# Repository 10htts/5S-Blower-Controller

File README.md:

# 5S Blower Controller

Open-source reference controller for a two-wire brushed-DC blower powered by a removable 5-series lithium-ion battery (approximately 15–21 V). The design uses a protected low-side N-MOSFET PWM stage, soft start, trigger filtering, voltage/current/temperature protection, an external physical fuse, and a latched fault requiring trigger release.

**Status: CAD CHECKS PASS; NOT YET APPROVED TO ORDER.** KiCad 10 reports zero DRC violations, zero unconnected items, zero schematic-parity issues, and zero ERC errors or warnings. The PCBWay review ZIP is generated, but motor, fuse, mechanical, transient, thermal, and first-article validation remain open. No regulatory certification is claimed.

See [architecture](docs/architecture.md), [wiring](docs/wiring.md), [safety](docs/safety.md), and [revision status](docs/revision-status.md). Firmware tests are host-side and do not replace hardware bring-up.

## Open and edit in KiCad

Open `hardware/blower-controller.kicad_pro` using **File → Open Existing Project** in KiCad. The project contains the editable schematic and PCB.

The canonical KiCad files are generated by `scripts/build_board.py`. A later regeneration will overwrite direct edits to the generated schematic and PCB, so save experimental manual edits under a different project name or port accepted changes into the generator and routing-repair sources.

## Rebuild and export

Run the deterministic board build with KiCad's bundled Python, then generate the current PCBWay review package:

```powershell
& "C:\Program Files\KiCad\10.0\bin\python.exe" scripts\build_board.py
python scripts\export_manufacturing.py --kicad-cli "C:\Program Files\KiCad\10.0\bin\kicad-cli.exe"
```

The current package is `manufacturing/pcbway-review-revC.zip`. It is suitable for PCBWay's Gerber viewer or quotation review, not authorization to place an order.

## Licensing

Hardware is licensed under CERN-OHL-S-2.0 (`LICENSE`). Firmware is GPLv3-or-later (`firmware/LICENSE`).

## Planned validation

Measure stall/start/run current, battery connector polarity, motor inductance, housing fit, fuse interruption behavior, and thermal rise before selecting production thresholds or ordering PCBs.

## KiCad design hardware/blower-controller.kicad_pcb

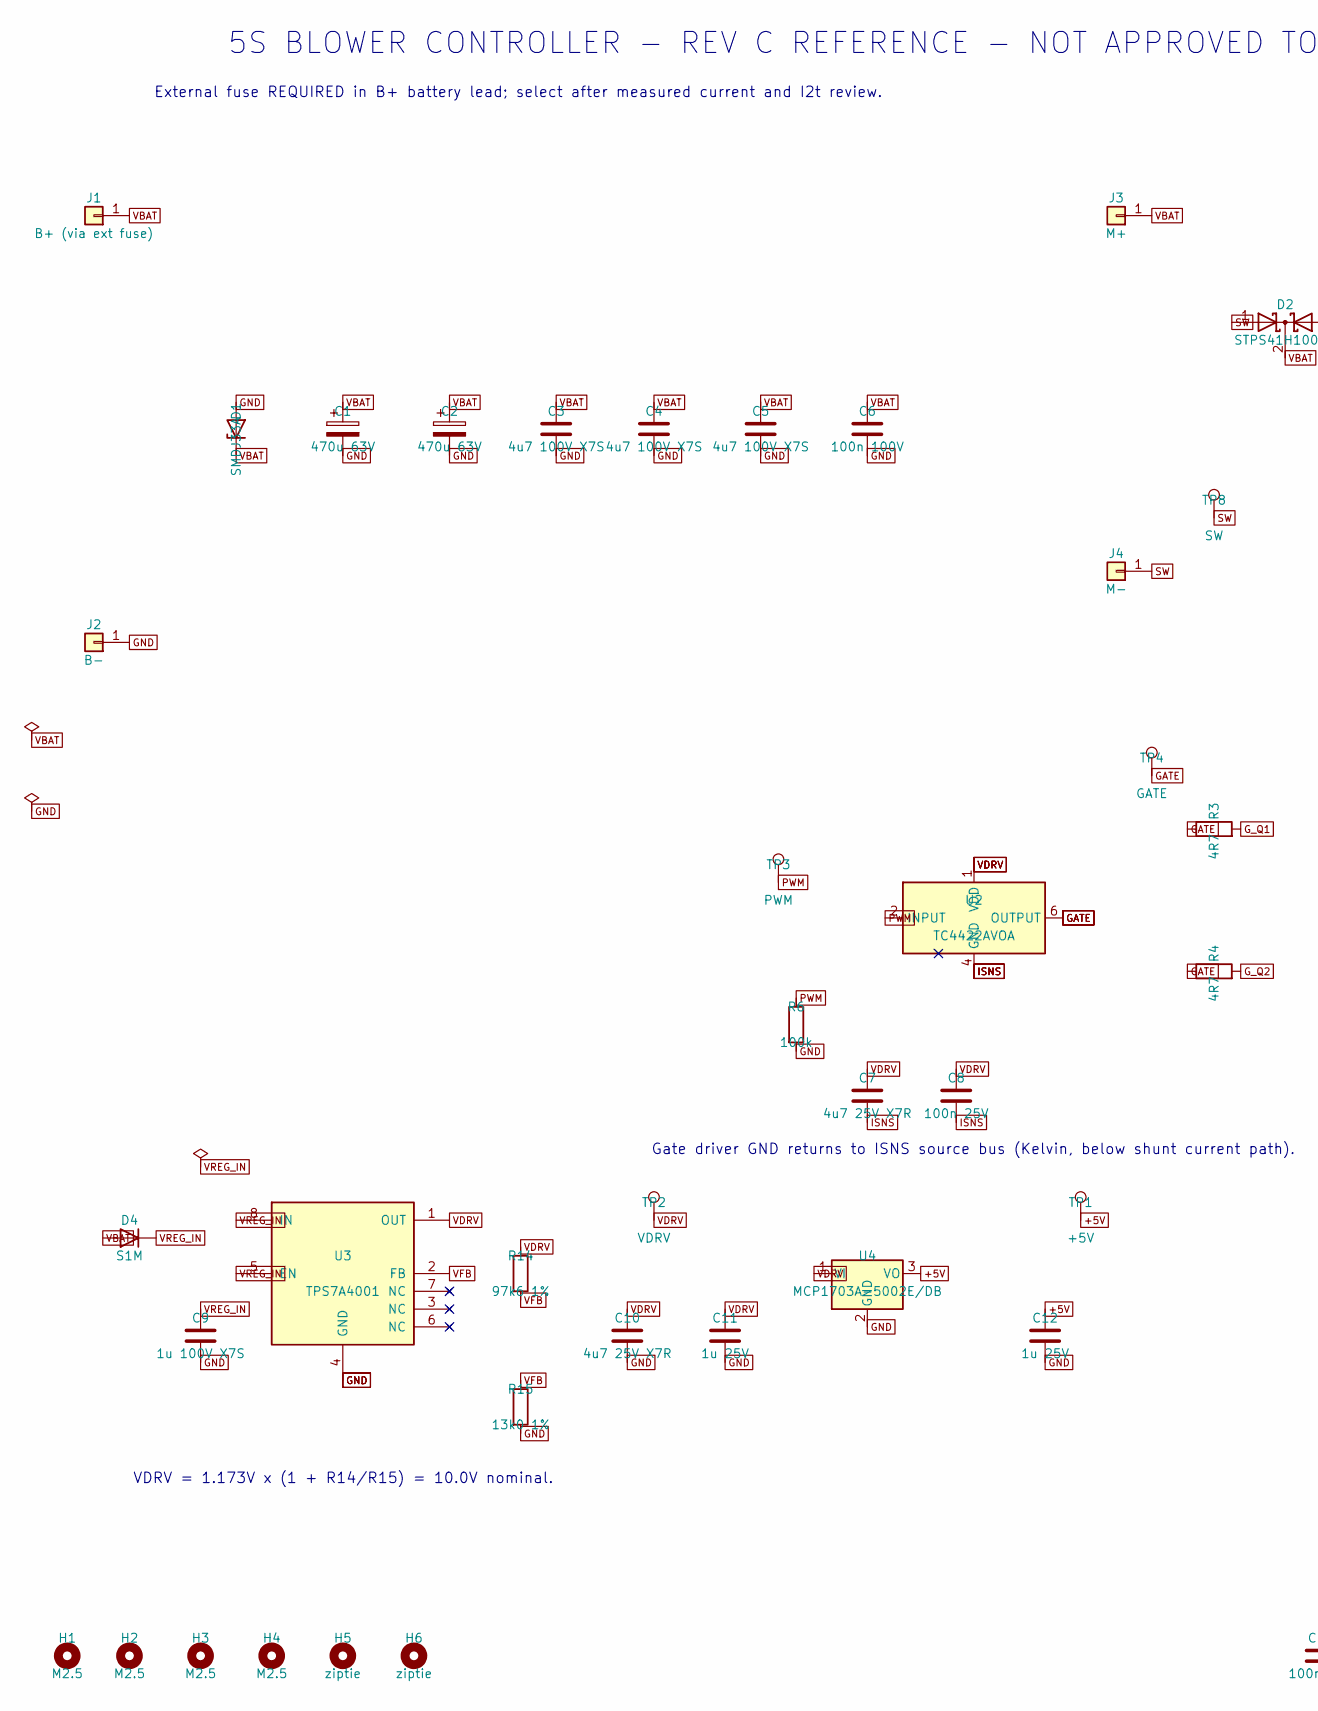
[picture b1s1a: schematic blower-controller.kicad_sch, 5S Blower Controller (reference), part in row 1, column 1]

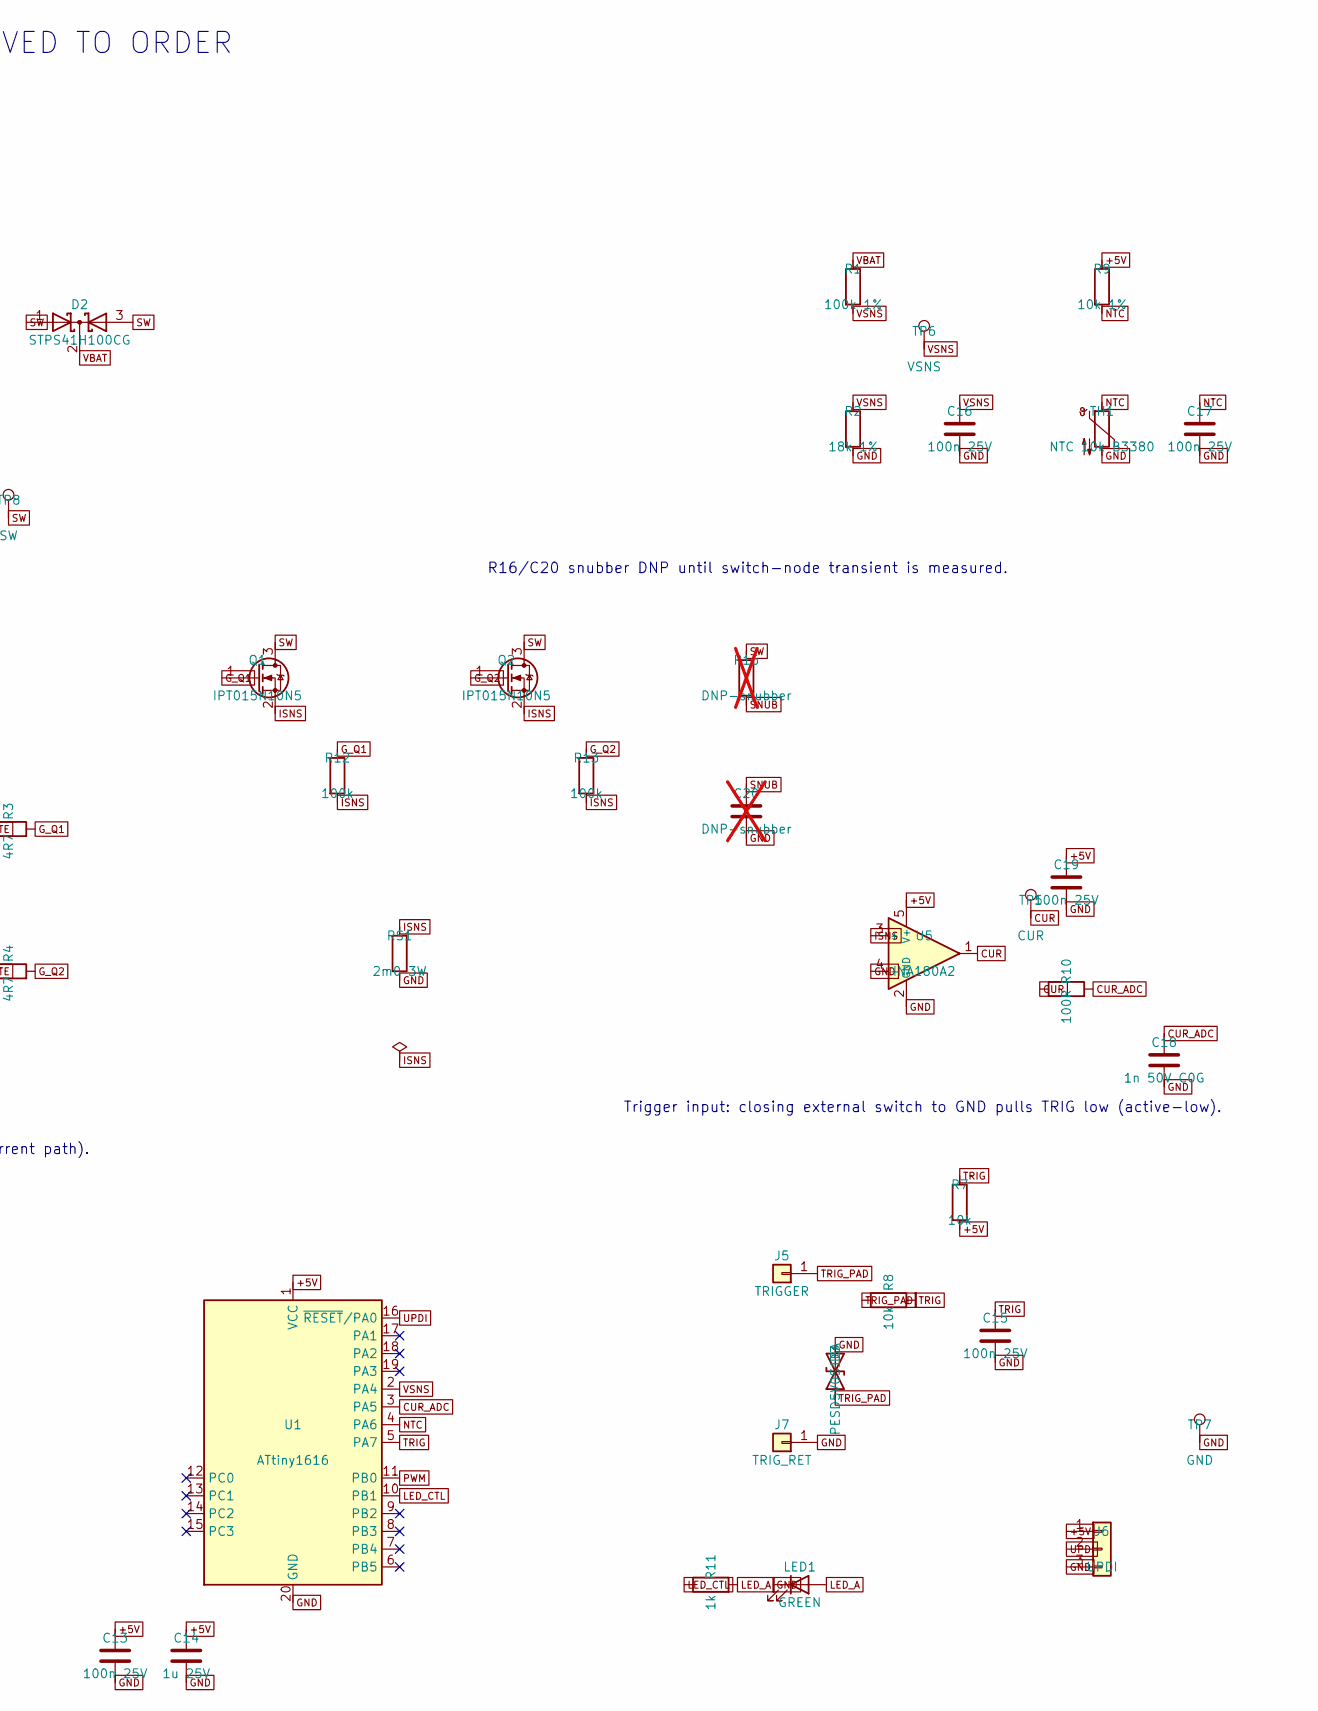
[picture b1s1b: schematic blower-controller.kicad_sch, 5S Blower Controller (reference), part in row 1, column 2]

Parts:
C1, C2: 470u 63V; CP_Radial_D12.5mm_P5.00mm; MPN UPW1J471MHD; LCSC UNVERIFIED
C3, C4, C5: 4u7 100V X7S; C_1210_3225Metric; MPN C3225X7S2A475K200AE; LCSC UNVERIFIED
C6: 100n 100V; C_0603_1608Metric; LCSC UNVERIFIED
C7, C10: 4u7 25V X7R; C_1206_3216Metric; LCSC UNVERIFIED
C8, C13, C15, C16, C17, C19: 100n 25V; C_0603_1608Metric; LCSC UNVERIFIED
C9: 1u 100V X7S; C_1210_3225Metric; LCSC UNVERIFIED
C11, C12, C14: 1u 25V; C_0603_1608Metric; LCSC UNVERIFIED
C18: 1n 50V C0G; C_0603_1608Metric; LCSC UNVERIFIED
C20: DNP-snubber; C_1210_3225Metric; LCSC UNVERIFIED; not fitted
D1: SMDJ33A; D_SMC; MPN SMDJ33A; LCSC UNVERIFIED
D2: STPS41H100CG; TO-263-3_TabPin2; MPN STPS41H100CG-TR; LCSC UNVERIFIED
D3: PESD5V0S1BA; D_SOD-323; MPN PESD5V0S1BA,115; LCSC C19224
D4: S1M; D_SMA; MPN S1M (onsemi); LCSC C232826
H1, H2, H3, H4: M2.5; MountingHole_2.7mm_M2.5; LCSC UNVERIFIED
H5, H6: ziptie; MountingHole_3.2mm_M3; LCSC UNVERIFIED
J1: B+ (via ext fuse); SolderWire-4sqmm_1x01_D3mm_OD6mm; LCSC UNVERIFIED
J2: B-; SolderWire-4sqmm_1x01_D3mm_OD6mm; LCSC UNVERIFIED
J3: M+; SolderWire-4sqmm_1x01_D3mm_OD6mm; LCSC UNVERIFIED
J4: M-; SolderWire-4sqmm_1x01_D3mm_OD6mm; LCSC UNVERIFIED
J5: TRIGGER; SolderWire-0.5sqmm_1x01_D0.9mm_OD2.1mm; LCSC UNVERIFIED
J6: UPDI; PinHeader_1x03_P2.54mm_Vertical; LCSC UNVERIFIED
J7: TRIG_RET; SolderWire-0.5sqmm_1x01_D0.9mm_OD2.1mm; LCSC UNVERIFIED
LED1: GREEN; LED_0603_1608Metric; MPN 19-217/GHC-YR1S2/3T; LCSC C72043
Q1, Q2: IPT015N10N5; Infineon_PG-HSOF-8-1; MPN IPT015N10N5ATMA1; LCSC C108964
R1: 100k 1%; R_0603_1608Metric; LCSC UNVERIFIED
R2: 18k 1%; R_0603_1608Metric; LCSC UNVERIFIED
R3, R4: 4R7; R_0805_2012Metric; LCSC UNVERIFIED
R6, R12, R13: 100k; R_0603_1608Metric; LCSC UNVERIFIED
R7, R8: 10k; R_0603_1608Metric; LCSC UNVERIFIED
R9: 10k 1%; R_0603_1608Metric; LCSC UNVERIFIED
R10: 100R; R_0603_1608Metric; LCSC UNVERIFIED
R11: 1k; R_0603_1608Metric; LCSC UNVERIFIED
R14: 97k6 1%; R_0603_1608Metric; LCSC UNVERIFIED
R15: 13k0 1%; R_0603_1608Metric; LCSC UNVERIFIED
R16: DNP-snubber; R_2512_6332Metric; LCSC UNVERIFIED; not fitted
RS1: 2m0 3W; R_Shunt_Vishay_WSR2_WSR3_KelvinConnection; MPN WSR32L000FEA; LCSC UNVERIFIED
TH1: NTC 10k B3380; R_0603_1608Metric; MPN NCP18XH103F03RB; LCSC C13564
TP1: +5V; TestPoint_Pad_D1.5mm; LCSC UNVERIFIED
TP2: VDRV; TestPoint_Pad_D1.5mm; LCSC UNVERIFIED
TP3: PWM; TestPoint_Pad_D1.5mm; LCSC UNVERIFIED
TP4: GATE; TestPoint_Pad_D1.5mm; LCSC UNVERIFIED
TP5: CUR; TestPoint_Pad_D1.5mm; LCSC UNVERIFIED
TP6: VSNS; TestPoint_Pad_D1.5mm; LCSC UNVERIFIED
TP7: GND; TestPoint_Pad_D1.5mm; LCSC UNVERIFIED
TP8: SW; TestPoint_Pad_D1.5mm; LCSC UNVERIFIED
U1: ATtiny1616; SOIC-20W_7.5x12.8mm_P1.27mm; MPN ATTINY1616-SNR; LCSC C614136
U2: TC4422AVOA; SOIC-8_3.9x4.9mm_P1.27mm; MPN TC4422AVOA; LCSC C37183
U3: TPS7A4001; MSOP-8-1EP_3x3mm_P0.65mm_EP1.68x1.88mm; MPN TPS7A4001DGNR; LCSC C55006
U4: MCP1703A-5002E/DB; SOT-223-3_TabPin2; MPN MCP1703A-5002E/DB; LCSC UNVERIFIED
U5: INA180A2; SOT-23-5; MPN INA180A2IDBVR; LCSC C192764

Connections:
+5V: C12.1, C13.1, C14.1, C19.1, J6.1, R7.2, R9.1, TP1.1, U1.1 (VCC), U4.3 (VO), U5.5 (V+)
CUR: R10.1, TP5.1, U5.1
CUR_ADC: C18.1, R10.2, U1.3 (PA5)
GATE: R3.1, R4.1, TP4.1, U2.6 (OUTPUT), U2.7 (OUTPUT)
GND: C1.2, C2.2, C3.2, C4.2, C5.2, C6.2, C9.2, C10.2, C11.2, C12.2, C13.2, C14.2, C15.2, C16.2, C17.2, C18.2, C19.2, C20.2, D1.2 (A), D3.2 (A2), J2.1, J6.3, J7.1, LED1.1 (K), R2.2, R6.2, R15.2, RS1.2, TH1.2, TP7.1, U1.20 (GND), U3.4 (GND), U3.9 (EP), U4.2 (GND), U5.2 (GND), U5.4 (-)
G_Q1: Q1.1 (G), R3.2, R12.1
G_Q2: Q2.1 (G), R4.2, R13.1
ISNS: C7.2, C8.2, Q1.2 (S), Q2.2 (S), R12.2, R13.2, RS1.1, U2.4 (GND), U2.5 (GND), U5.3 (+)
LED_A: LED1.2 (A), R11.2
LED_CTL: R11.1, U1.10 (PB1)
NTC: C17.1, R9.2, TH1.1, U1.4 (PA6)
PWM: R6.1, TP3.1, U1.11 (PB0), U2.2 (INPUT)
SNUB: C20.1, R16.2
SW: D2.1 (A), D2.3 (A), J4.1, Q1.3 (D), Q2.3 (D), R16.1, TP8.1
TRIG: C15.1, R7.1, R8.2, U1.5 (PA7)
TRIG_PAD: D3.1 (A1), J5.1, R8.1
UPDI: J6.2, U1.16 (~RESET/PA0)
VBAT: C1.1, C2.1, C3.1, C4.1, C5.1, C6.1, D1.1 (K), D2.2 (K), D4.2 (A), J1.1, J3.1, R1.1
VDRV: C7.1, C8.1, C10.1, C11.1, R14.1, TP2.1, U2.1 (VDD), U2.8 (VDD), U3.1 (OUT), U4.1 (VI)
VFB: R14.2, R15.1, U3.2 (FB)
VREG_IN: C9.1, D4.1 (K), U3.5 (EN), U3.8 (IN)
VSNS: C16.1, R1.2, R2.1, TP6.1, U1.2 (PA4)

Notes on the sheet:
5S BLOWER CONTROLLER - REV C REFERENCE - NOT APPROVED TO ORDER
External fuse REQUIRED in B+ battery lead; select after measured current and I2t review.
Gate driver GND returns to ISNS source bus (Kelvin, below shunt current path).
R16/C20 snubber DNP until switch-node transient is measured.
Trigger input: closing external switch to GND pulls TRIG low (active-low).
VDRV = 1.173V x (1 + R14/R15) = 10.0V nominal.

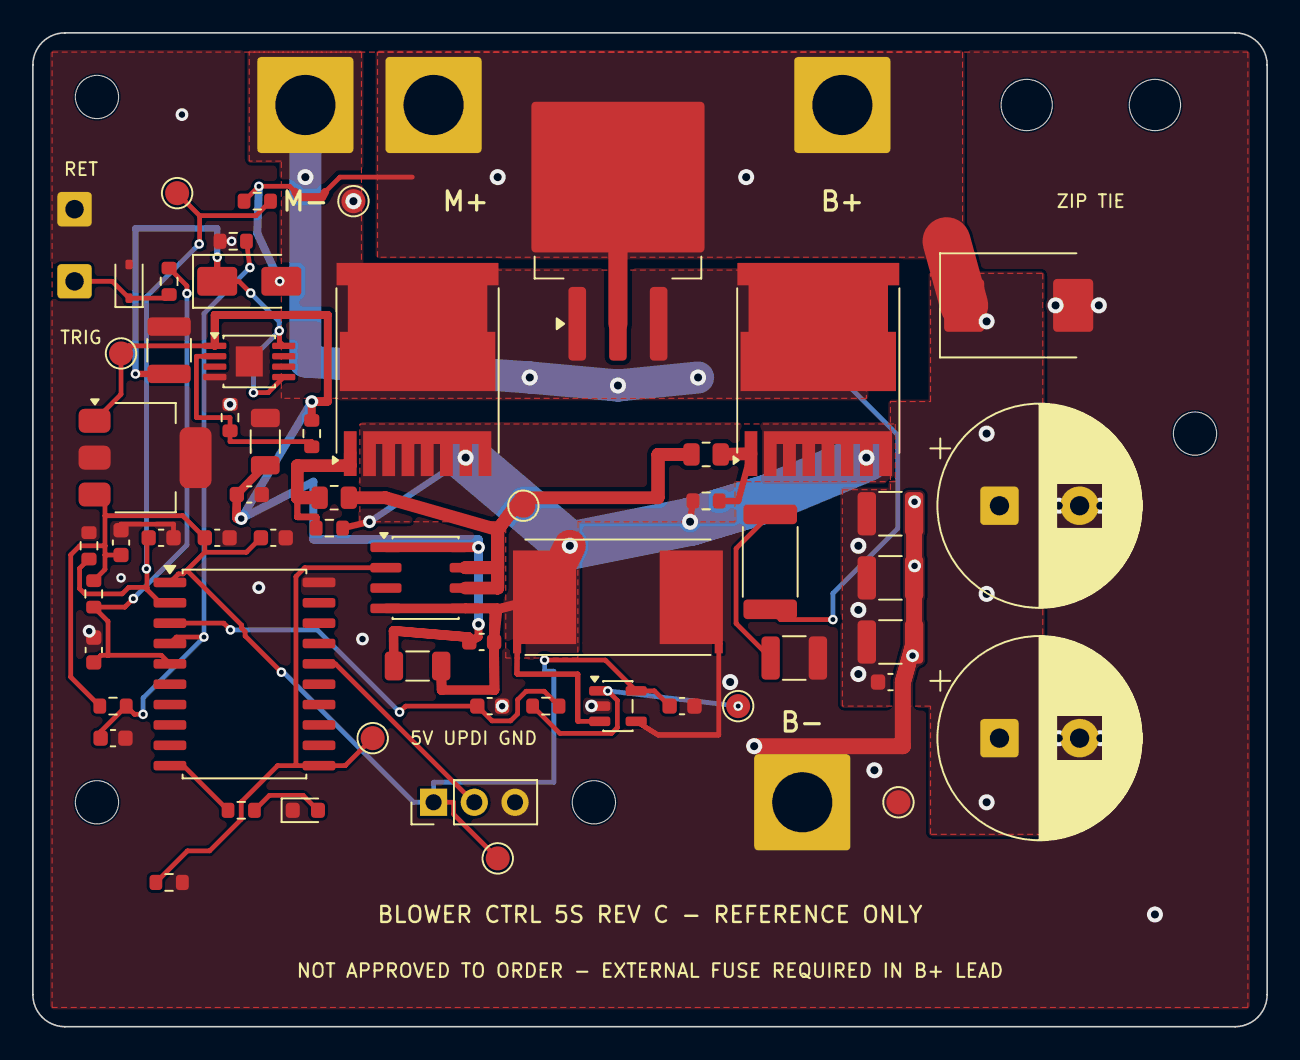
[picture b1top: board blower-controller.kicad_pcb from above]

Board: 2 copper layers, 77.0 x 62.0 mm, 70 parts (0 on the bottom side), 22 nets.

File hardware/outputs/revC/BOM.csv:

"References","Value","Footprint","Manufacturer Part Number","LCSC","Quantity","DNP"
"C1,C2","470u 63V","Capacitor_THT:CP_Radial_D12.5mm_P5.00mm","UPW1J471MHD","UNVERIFIED","2",""
"C3-C5","4u7 100V X7S","Capacitor_SMD:C_1210_3225Metric","C3225X7S2A475K200AE","UNVERIFIED","3",""
"C6","100n 100V","Capacitor_SMD:C_0603_1608Metric","","UNVERIFIED","1",""
"C7,C10","4u7 25V X7R","Capacitor_SMD:C_1206_3216Metric","","UNVERIFIED","2",""
"C8,C13,C15-C17,C19","100n 25V","Capacitor_SMD:C_0603_1608Metric","","UNVERIFIED","6",""
"C9","1u 100V X7S","Capacitor_SMD:C_1210_3225Metric","","UNVERIFIED","1",""
"C11,C12,C14","1u 25V","Capacitor_SMD:C_0603_1608Metric","","UNVERIFIED","3",""
"C18","1n 50V C0G","Capacitor_SMD:C_0603_1608Metric","","UNVERIFIED","1",""
"D1","SMDJ33A","Diode_SMD:D_SMC","SMDJ33A","UNVERIFIED","1",""
"D2","STPS41H100CG","Package_TO_SOT_SMD:TO-263-3_TabPin2","STPS41H100CG-TR","UNVERIFIED","1",""
"D3","PESD5V0S1BA","Diode_SMD:D_SOD-323","PESD5V0S1BA,115","C19224","1",""
"D4","S1M","Diode_SMD:D_SMA","S1M (onsemi)","C232826","1",""
"J6","UPDI","Connector_PinHeader_2.54mm:PinHeader_1x03_P2.54mm_Vertical","","UNVERIFIED","1",""
"LED1","GREEN","LED_SMD:LED_0603_1608Metric","19-217/GHC-YR1S2/3T","C72043","1",""
"Q1,Q2","IPT015N10N5","Package_TO_SOT_SMD:Infineon_PG-HSOF-8-1","IPT015N10N5ATMA1","C108964","2",""
"R1","100k 1%","Resistor_SMD:R_0603_1608Metric","","UNVERIFIED","1",""
"R2","18k 1%","Resistor_SMD:R_0603_1608Metric","","UNVERIFIED","1",""
"R3,R4","4R7","Resistor_SMD:R_0805_2012Metric","","UNVERIFIED","2",""
"R6,R12,R13","100k","Resistor_SMD:R_0603_1608Metric","","UNVERIFIED","3",""
"R7,R8","10k","Resistor_SMD:R_0603_1608Metric","","UNVERIFIED","2",""
"R9","10k 1%","Resistor_SMD:R_0603_1608Metric","","UNVERIFIED","1",""
"R10","100R","Resistor_SMD:R_0603_1608Metric","","UNVERIFIED","1",""
"R11","1k","Resistor_SMD:R_0603_1608Metric","","UNVERIFIED","1",""
"R14","97k6 1%","Resistor_SMD:R_0603_1608Metric","","UNVERIFIED","1",""
"R15","13k0 1%","Resistor_SMD:R_0603_1608Metric","","UNVERIFIED","1",""
"RS1","2m0 3W","Resistor_SMD:R_Shunt_Vishay_WSR2_WSR3_KelvinConnection","WSR32L000FEA","UNVERIFIED","1",""
"TH1","NTC 10k B3380","Resistor_SMD:R_0603_1608Metric","NCP18XH103F03RB","C13564","1",""
"U1","ATtiny1616","Package_SO:SOIC-20W_7.5x12.8mm_P1.27mm","ATTINY1616-SNR","C614136","1",""
"U2","TC4422AVOA","Package_SO:SOIC-8_3.9x4.9mm_P1.27mm","TC4422AVOA","C37183","1",""
"U3","TPS7A4001","Package_SO:MSOP-8-1EP_3x3mm_P0.65mm_EP1.68x1.88mm","TPS7A4001DGNR","C55006","1",""
"U4","MCP1703A-5002E/DB","Package_TO_SOT_SMD:SOT-223-3_TabPin2","MCP1703A-5002E/DB","UNVERIFIED","1",""
"U5","INA180A2","Package_TO_SOT_SMD:SOT-23-5","INA180A2IDBVR","C192764","1",""

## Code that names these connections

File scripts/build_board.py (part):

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- U3     TPS7A4001DGNR     7-100V in, 50mA, FB=1.173V typ, MSOP-8 PowerPAD:
         1=OUT 2=FB 3=NC 4=GND 5=EN 6=NC 7=NC 8=IN, EP=GND. LCSC C55006.
- U4     MCP1703A-5002E/DB 16V in, 250mA, SOT-223: 1=VIN 2=GND(tab) 3=VOUT.
- U1     ATTINY1616-SNR    SOIC-20: 1=VDD 20=GND 16=UPDI 11=PB0(TCA0 WO0)
         10=PB1 2=PA4/AIN4 3=PA5/AIN5 4=PA6/AIN6 5=PA7/AIN7. LCSC C614136.
- U5     INA180A2IDBVR     gain 50, CM -0.2..26V, SOT-23-5:
         1=OUT 2=GND 3=IN+ 4=IN- 5=VS. LCSC C192764.
- RS1    WSR32L000FEA      2mOhm 1% 3W metal strip, Kelvin by split-pad layout.
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    ("GND", "F", 0.3,
     ["RS1.SENSE2", (42.79, 43.8), (39.0, 43.8), "U5.4"]),

    # Driver supply decoupling: both VDD pins share the local VDRV node;
    # C8 is the closest HF capacitor and C7 is the local bulk capacitor.
    # The U2.8-to-C8 leg is routed on B.Cu (via drop just south of U2's
    # body, via rise just north of C8) because the direct F.Cu path at
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     ["R1.1", (13.175, 13.0), (14.5, 13.6), "D4.2"]),
    ("VBAT", "F", 0.5,
     [(14.5, 13.6), (21.8, 13.5)]),
    # VREG_IN: D4.1/U3.8/C9.1 are wired on B.Cu (dropping straight through
    # vias at each pad) so this whole branch passes underneath the F.Cu
    # VDRV perimeter route without touching it.  U3.5 (the other east-side
    # VREG_IN pin) is picked up separately by a short F.Cu lane just below
    # U3's body (y=22.2, between the EP/GND row and the R14/R15/C10 stack)
    # that lands on C9.1, tying the whole net together.
    ("VREG_IN", "F", 0.4, ["U3.8", (15.65, 18.8), (15.0, 18.8)]),
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    ("VREG_IN", "F", 0.4, ["U3.5", (15.65, 22.2)]),
    ("VREG_IN", "B", 0.4, [(15.65, 22.2), "C9.1"]),
    # VFB (U3.2) stays on F.Cu the whole way: west first (clear of U3's own
    # pin pitch), south past the VREG_IN B.Cu run (different layer, so no
    # conflict), then to R15.1.
    ("VFB", "F", 0.3,
     ["U3.2", (10.2, 20.175), (10.2, 23.2), "R15.1"]),
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
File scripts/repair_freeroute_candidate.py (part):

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        track_pool, "VBAT", (18.2381, 9.9182), (16.3654, 9.9182), expected=1
    )
    tracks_to_remove += select_tracks(
        track_pool, "VDRV", (17.4, 23.0), (17.4, 21.825), expected=1
    )
    tracks_to_remove += select_tracks(
        track_pool, "G_Q1", (16.5, 26.25), (19.8, 26.25), expected=2
    )
    tracks_to_remove += select_tracks(
        track_pool, "G_Q1", (16.5, 29.0), (16.5, 26.25), expected=1
    )
    tracks_to_remove += select_tracks(
        track_pool, "NTC", (17.675, 12.5), (15.6808, 12.5), expected=1
    )
    tracks_to_remove += select_tracks(
        track_pool, "NTC", (15.6808, 12.5), (13.5409, 14.6399), expected=1
    )
    tracks_to_remove += select_tracks(
        track_pool, "+5V", (25.0, 46.7483), (31.9237, 39.8246), expected=1
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

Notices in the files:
hardware/blower-controller.kicad_sch:
open hardware - CERN-OHL-S-2.0
